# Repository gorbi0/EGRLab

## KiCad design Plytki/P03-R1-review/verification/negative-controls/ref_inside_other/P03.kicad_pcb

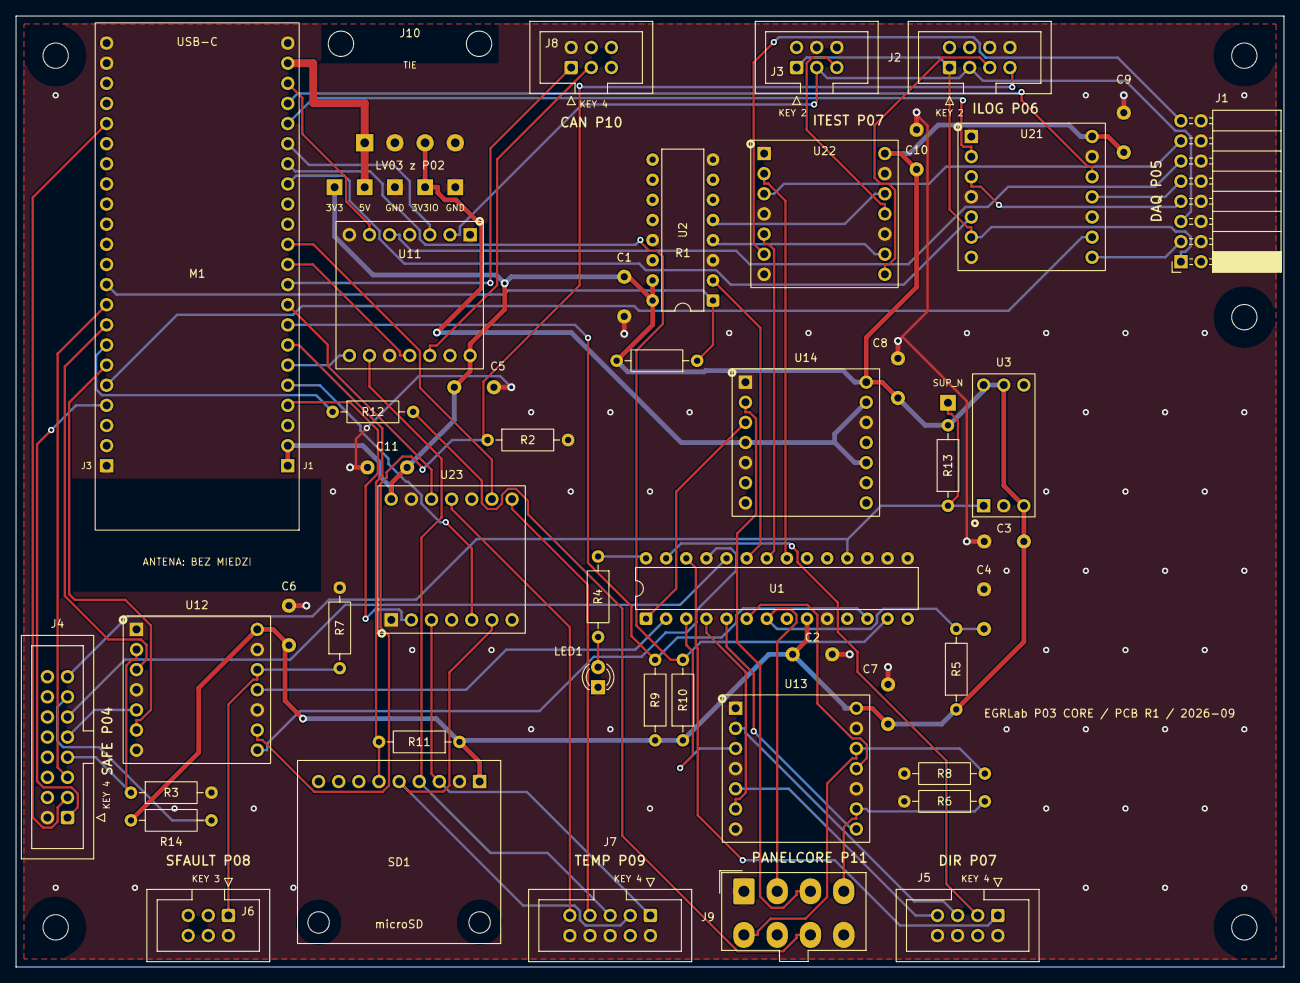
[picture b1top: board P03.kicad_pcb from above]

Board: 2 copper layers, 160.0 x 120.0 mm, 59 parts (0 on the bottom side), 73 nets.

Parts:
C1, C2, C3, C4, C5, C6, C7, C8, C9, C10, C11: 100nF / X7R; C_Vishay_K15_H5_P5
H1, H2, H3, H4, H5: M3 NPTH
J1: DAQ B2B / RA socket 2x8; PinSocket_2x08_P2.54mm_Horizontal
J2: ILOG / IDC 2x4 KEY 2; IDC-Header_2x04_P2.54mm_Vertical
J3: ITEST / IDC 2x3 KEY 2; IDC-Header_2x03_P2.54mm_Vertical
J4: SAFE / IDC 2x8 KEY 4; IDC-Header_2x08_P2.54mm_Vertical
J5: DIR / IDC 2x4 KEY 4; IDC-Header_2x04_P2.54mm_Vertical
J6: SFAULT / IDC 2x3 KEY 3; IDC-Header_2x03_P2.54mm_Vertical
J7: TEMP / IDC 2x5 KEY 4; IDC-Header_2x05_P2.54mm_Vertical
J8: CAN / IDC 2x3 KEY 4; IDC-Header_2x03_P2.54mm_Vertical
J9: PANELCORE / Mini-Fit Jr 8p; Molex_Mini-Fit_Jr_5566-08A_2x04_P4.20mm_Vertical
J10: LV03 / soldered harness; Pigtail_LV_4xAWG22_P3.81
LED1: GREEN 3mm / STATUS; LED_D3.0mm
M1: Waveshare ESP32-S3-DEV-KIT-N32R16V; Waveshare_ESP32-S3-DEV-KIT_2x22_W22.86
R1, R2, R3, R5, R6, R7, R8, R11, R13: 10K / 1%; R_Axial_DIN0207_L6.3mm_D2.5mm_P10.16mm_Horizontal
R4: 1K / 1%; R_Axial_DIN0207_L6.3mm_D2.5mm_P10.16mm_Horizontal
R9, R10: 4K7 / 1%; R_Axial_DIN0207_L6.3mm_D2.5mm_P10.16mm_Horizontal
R12: 330R / 1%; R_Axial_DIN0207_L6.3mm_D2.5mm_P10.16mm_Horizontal
R14: 0R; R_Axial_DIN0207_L6.3mm_D2.5mm_P10.16mm_Horizontal
SD1: Adafruit 4682 microSD (3V); Adafruit_4682_microSD_1x09
TP1: 5V_SYS; TestPad_1
TP2: 3V3_CORE; TestPad_1
TP3: 3V3_IO; TestPad_1
TP4, TP6: GND; TestPad_1
TP5: SUP_N; TestPad_1
U1: MCP23017-E/SP; DIP-28_W7.62mm
U2: SN74HC139N; DIP-16_W7.62mm
U3: TPS3808G33DBVR / PA0085; Adapter_SOT23-6_DIP6_W15.24_ChipQuik_PA0085
U11, U12, U13, U14, U21, U22, U23: 74LVC125A / SO14 adapter; Adapter_SO14_DIP14_W15.24_Kamami575068

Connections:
3V3_CORE: C1.1, C2.1, C3.1, C5.1, C6.1, C7.1, C8.1, C9.1, C10.1, C11.1, M1.J1-1, M1.J1-2, R1.2, R5.1, R9.1, R10.1, R11.1, R13.2, R14.1, SD1.1, TP2.1, U1.9, U2.15, U2.16, U3.3, U3.5, U3.6, U11.14, U12.14, U13.14, U14.14, U21.14, U22.14, U23.14
3V3_IO: J10.3, TP3.1, U14.4, U14.10, U14.13
/5V_SYS: J10.1, M1.J1-21, TP1.1
/CURRENT_CS_N: M1.J3-10, R1.1, U2.1
/I2C_SCL: M1.J1-8, R9.2, U1.12
/I2C_SDA: M1.J1-16, R10.2, U1.13
/IO/ADC_BUSY: J1.11, U11.5
/IO/ADC_CONVST: J1.9, U21.11
/IO/ADC_CS: J1.7, U21.3
/IO/ADC_DOUTA: J1.5, J2.3, J3.3, U11.2
/IO/ADC_RESET: J1.13, U22.3
/IO/ADC_SCLK: J1.1, J2.1, J3.1, U21.6
/IO/ADC_SDI: J1.3, U21.8
/IO/CAN_RX: J8.3, U11.12
/IO/CS_ILOG_N: J2.5, U22.8
/IO/CS_ITEST_N: J3.5, U22.11
/IO/ENA_DIAG: J5.5, U13.2
/IO/ENB_DIAG: J5.7, U13.5
/IO/HW_ARMED: J4.7, R3.1, U12.2
/IO/INTERLOCK: J4.9, U12.5
/IO/LOGGER_CLEAR: J9.4, R6.1, U13.9
/IO/LOGGER_CURRENT_OK: J2.7, R2.1, U12.9
/IO/MEAS_EN: J1.15, U22.6
/IO/SENSOR_HEALTHY: J6.1, R7.1, U12.12
/IO/TC1_CS: J7.7, U23.8
/IO/TC2_CS: J7.9, U23.11
/IO/TEST_KEY: J9.3, U14.2
/IO/TEST_PRESENT: J9.5, R8.1, U13.12
/LED_A: LED1.2, R4.2
/MEAS_BANK: U1.23, U2.2
/SCOPE_TRIG: M1.J3-7, R12.1
/SD_CS: M1.J1-7, R11.2, SD1.6
/STATUS_LED: R4.1, U1.28
ADC_BUSY_CORE: M1.J1-20, U11.6
ADC_CONVST_SRC: M1.J1-19, U21.12
ADC_CS_SRC: M1.J1-18, U21.2
ADC_DOUTA_CORE: M1.J1-17, U11.3
ADC_RESET_SRC: U1.21, U22.2
ADC_SCLK_SRC: M1.J1-15, U21.5
ADC_SDI_SRC: M1.J3-5, U21.9
CAN_RX_CORE: M1.J1-11, U11.11
CAN_TX: J8.1, M1.J1-10
CORE_LINK: J4.13, R14.2
CS_ILOG_N_SRC: U2.4, U22.9
CS_ITEST_N_SRC: U2.5, U22.12
ENA_DIAG_CORE: U1.3, U13.3
ENB_DIAG_CORE: U1.4, U13.6
GND: C1.2, C2.2, C3.2, C4.2, C5.2, C6.2, C7.2, C8.2, C9.2, C10.2, C11.2, J1.4, J1.6, J1.8, J1.10, J1.12, J1.14, J1.16, J2.4, J2.6, J2.8, J3.4, J3.6, J4.2, J4.6, J4.8, J4.10, J4.12, J4.14, J4.16, J5.2, J5.6, J5.8, J6.2, J7.2, J7.6, J7.8, J7.10, J8.2, J9.1, J9.8, J10.2, J10.4, LED1.1, M1.J1-22, M1.J3-1, M1.J3-21, M1.J3-22, R2.2, R3.2, R6.2, R7.2, R8.2, SD1.2, TP4.1, TP6.1, U1.10, U1.15, U1.16, U1.17, U2.3, U2.8, U2.13, U2.14, U3.2, U11.1, U11.4, U11.7, U11.10, U11.13, U12.1, U12.4, U12.7, U12.10, U12.13, U13.1, U13.4, U13.7, U13.10, U13.13, U14.1, U14.5, U14.7, U14.9, U14.12, U21.1, U21.4, U21.7, U21.10, U21.13, U22.1, U22.4, U22.7, U22.10, U22.13, U23.1, U23.4, U23.7, U23.10, U23.13
HEARTBEAT: J4.3, M1.J3-18
HW_ARMED_CORE: M1.J3-8, U12.3
INTERLOCK_CORE: M1.J3-6, U12.6
LOGGER_CLEAR_CORE: U1.5, U13.8
LOGGER_CURRENT_OK_CORE: U1.25, U12.8
MARK: C4.1, J9.2, R5.2, U1.7
MCU_ARM: J4.5, M1.J3-9
MEAS_EN_SRC: U1.22, U22.5
MOTOR_INA: J5.1, U1.26
MOTOR_INB: J5.3, U1.27
N_J_SCOPE_HOT: J9.7, R12.2
PWM: J4.1, M1.J3-4
SENSOR_ENABLE: J4.11, U1.24
SENSOR_HEALTHY_CORE: U1.2, U12.11
SPI3_MISO: J7.5, SD1.4, U11.9
SPI3_MISO_CORE: M1.J1-6, U11.8
SPI3_MOSI: J7.3, SD1.5, U23.6
SPI3_MOSI_SRC: M1.J1-5, U23.5
SPI3_SCLK: J7.1, SD1.3, U23.3
SPI3_SCLK_SRC: M1.J1-4, U23.2
SUP_N: J4.15, R13.1, TP5.1, U1.18, U3.1
TC1_CS_SRC: M1.J1-12, U23.9
TC2_CS_SRC: M1.J1-9, U23.12
TEST_KEY_CORE: U1.1, U14.3
TEST_PRESENT_CORE: U1.6, U13.11
